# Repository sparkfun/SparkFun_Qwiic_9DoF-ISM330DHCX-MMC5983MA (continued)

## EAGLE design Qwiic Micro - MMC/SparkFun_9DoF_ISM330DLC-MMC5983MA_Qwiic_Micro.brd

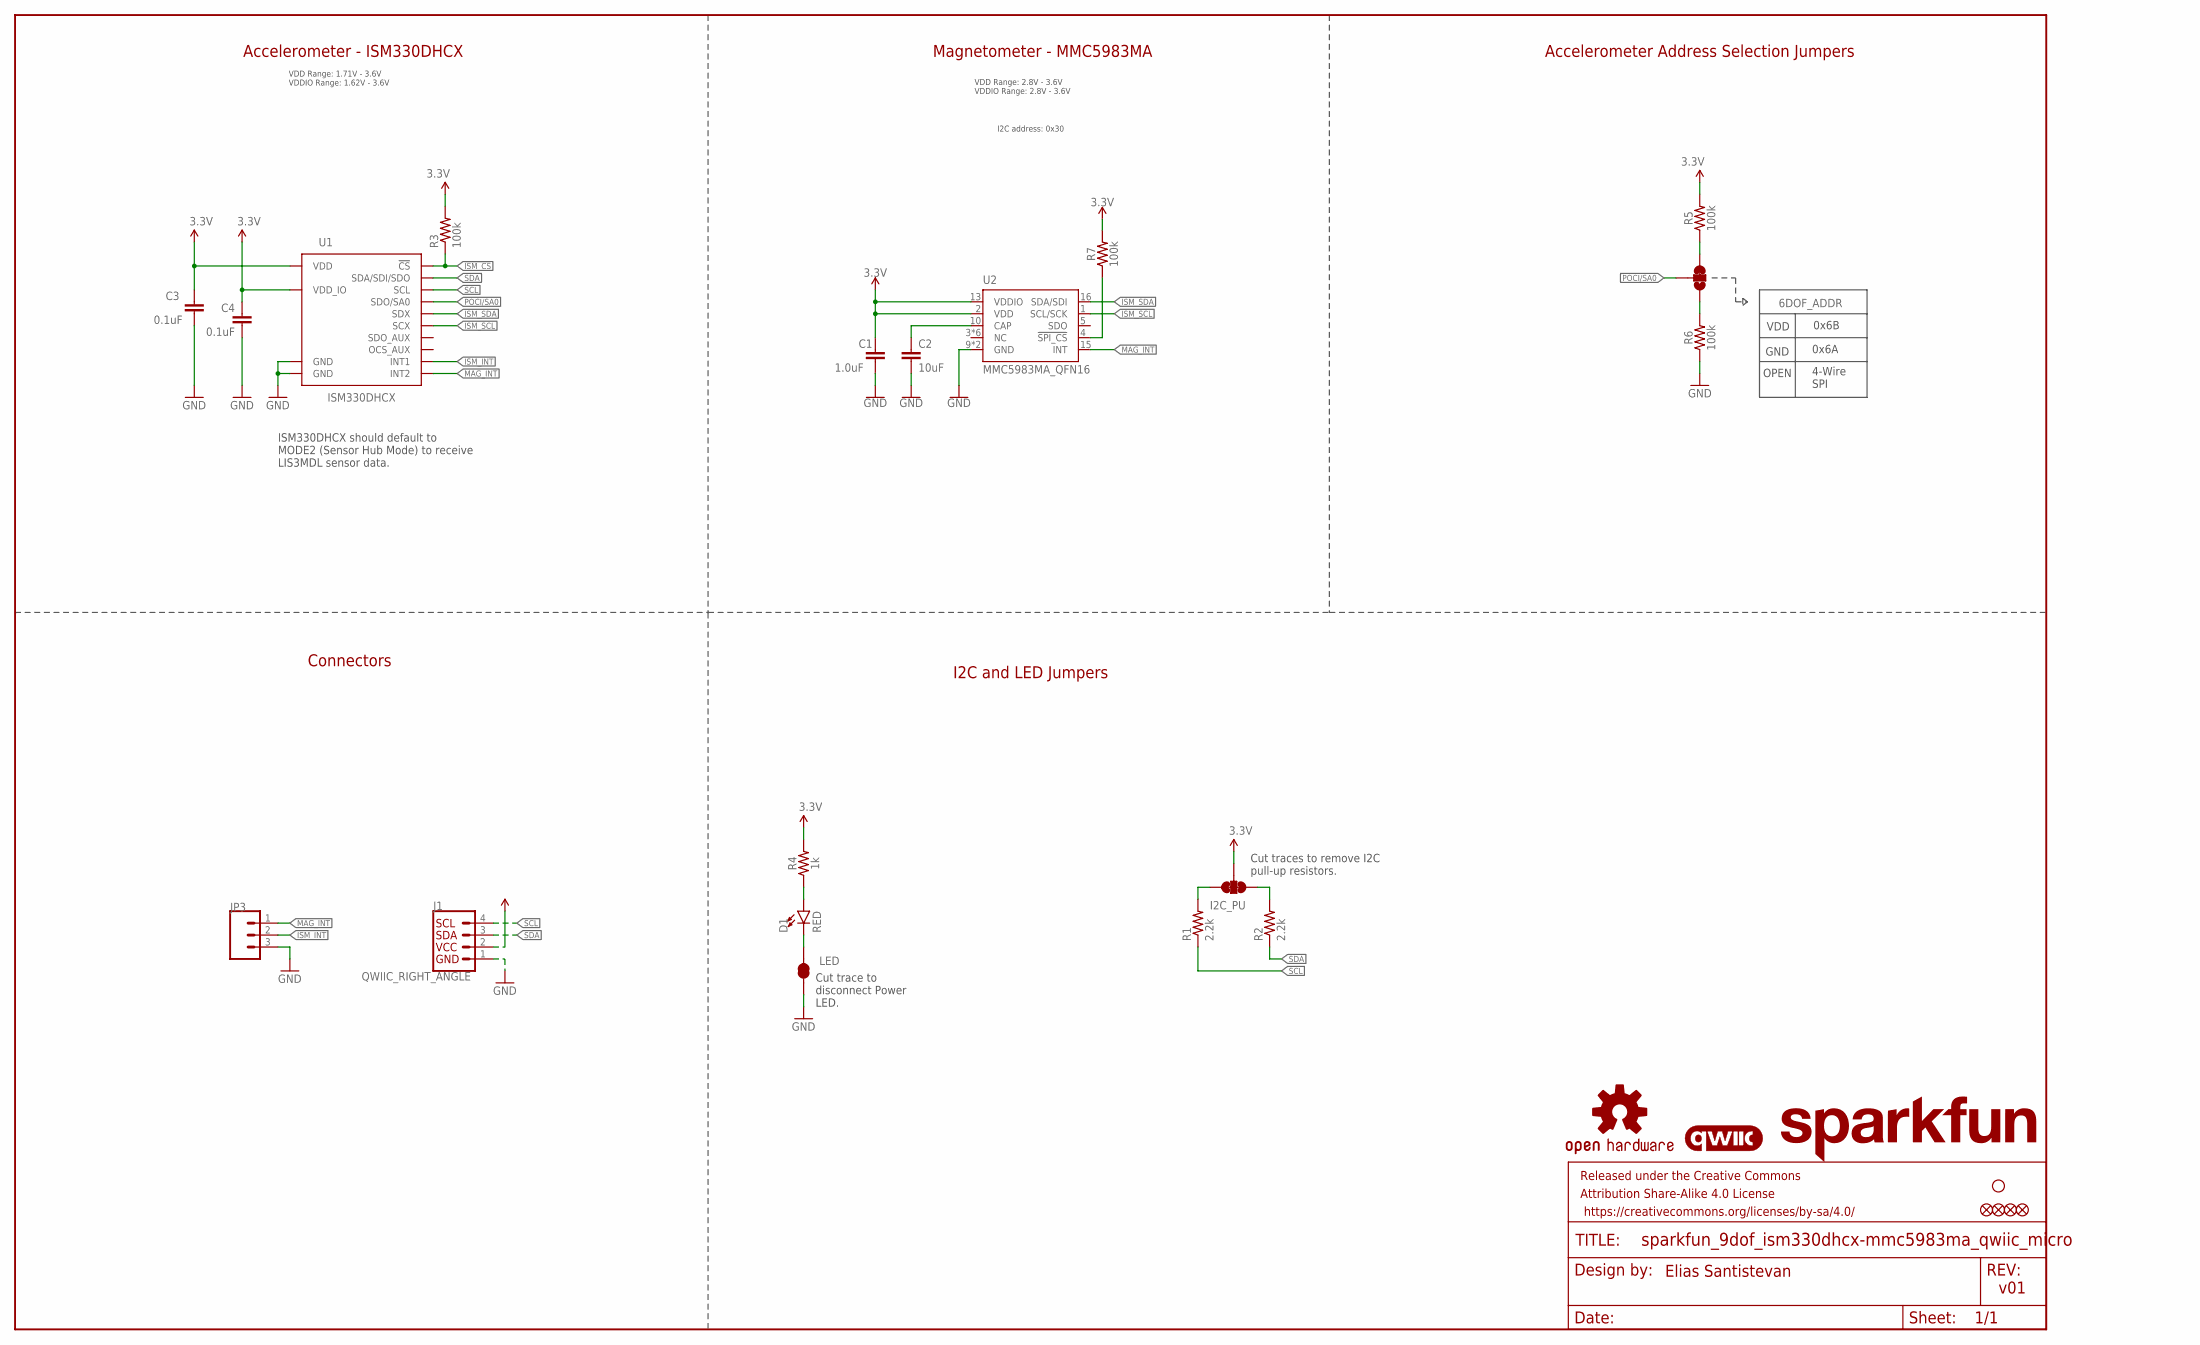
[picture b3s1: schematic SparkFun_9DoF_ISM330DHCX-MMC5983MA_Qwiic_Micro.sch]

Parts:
6DOF_ADDR: JUMPER-SMT_3_1-NC_TRACE_SILK; SMT-JUMPER_3_1-NC_TRACE_SILK
C1: 1.0uF; 0402-TIGHT
C2: 10uF; 0402-TIGHT
C3, C4: 0.1uF; 0402-TIGHT
D1: RED; 0402-TIGHT
FD1, FD2: FIDUCIALUFIDUCIAL; FIDUCIAL-MICRO
FID1, FID2: FIDUCIALUFIDUCIAL; FIDUCIAL-MICRO
FRAME2: FRAME-LEDGER; CREATIVE_COMMONS
I2C_PU: S_MODE; SMT-JUMPER_3_2-NC_TRACE_SILK
J1: QWIIC_RIGHT_ANGLE; JST04_1MM_RA
JP3: IO; 1X03_NO_SILK
LED: JUMPER-SMT_2_NC_TRACE_SILK; SMT-JUMPER_2_NC_TRACE_SILK
LOGO1: QWIIC_LOGO_4MM; QWIIC_4MM
LOGO2: OSHW-LOGOMINI; OSHW-LOGO-MINI
LOGO3: SFE_LOGO_NAMEBLANK; BLANK
R1, R2: 2.2k; 0402-TIGHT
R3, R5, R6, R7: 100k; 0402-TIGHT
R4: 1k; 0402-TIGHT
STANDOFF2: STAND-OFFTIGHT; STAND-OFF-TIGHT
U1: ISM330DHCX; LGA-14L
U2: MMC5983MA_QFN16; LGA-16-3X3MM-4X4PINS

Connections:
3.3V: C1.1, C3.1, C4.1, I2C_PU.2, J1.2, R3.2, R4.2, R5.2, R7.2, U1.P5 (VDD_IO), U1.P8 (VDD), U2.2 (VDD), U2.13 (VDDIO)
!ISM_CS!: R3.1, U1.P12 (!CS!)
!MAG_CS!: R7.1, U2.4 (!SPI_CS!)
CAP: C2.1, U2.10 (CAP)
GND: C1.2, C2.2, C3.2, C4.2, J1.1, JP3.3, LED.1, R6.1, U1.P6 (GND), U1.P7 (GND), U2.9 (GND), U2.11 (GND)
ISM_INT: JP3.2, U1.P4 (INT1)
ISM_SCL: U1.P3 (SCX), U2.1 (SCL/SCK)
ISM_SDA: U1.P2 (SDX), U2.16 (SDA/SDI)
MAG_INT: JP3.1, U1.P9 (INT2), U2.15 (INT)
unnamed: 6DOF_ADDR.3, R5.1
unnamed: D1.A, R4.1
unnamed: D1.C, LED.2
unnamed: I2C_PU.1, R1.2
unnamed: I2C_PU.3, R2.2
unnamed: 6DOF_ADDR.1, R6.2
POCI/SA0: 6DOF_ADDR.2, U1.P1 (SDO/SA0)
SCL: J1.4, R1.1, U1.P13 (SCL)
SDA: J1.3, R2.1, U1.P14 (SDA/SDI/SDO)

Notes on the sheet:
Accelerometer - ISM330DHCX
Cut traces to remove I2C pull-up resistors.
ISM330DHCX should default to MODE2 (Sensor Hub Mode) to receive LIS3MDL sensor data.
VDD Range: 1.71V - 3.6V VDDIO Range: 1.62V - 3.6V
v01
Cut trace to disconnect Power LED.
Connectors
VDD
GND
OPEN
0x6B
0x6A
4-Wire SPI
Elias Santistevan
VDD Range: 2.8V - 3.6V VDDIO Range: 2.8V - 3.6V
Magnetometer - MMC5983MA
Accelerometer Address Selection Jumpers
I2C and LED Jumpers
I2C address: 0x30

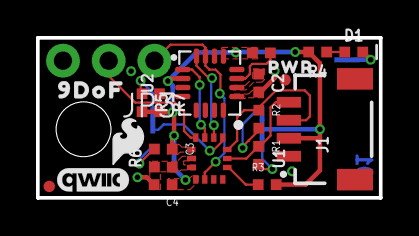
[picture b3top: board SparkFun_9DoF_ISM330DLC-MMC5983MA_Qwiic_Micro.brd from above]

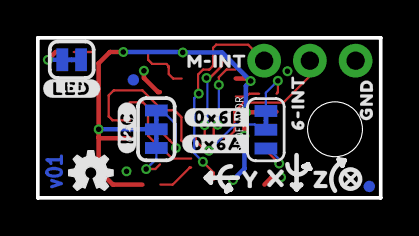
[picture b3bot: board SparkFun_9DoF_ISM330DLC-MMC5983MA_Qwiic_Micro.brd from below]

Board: 2 copper layers, 19.1 x 8.9 mm, 41 parts (16 on the bottom side), 18 nets.

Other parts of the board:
U$1: GND4
U$2: M#INT8
U$3: 6#INT8
U$4: #0X6A#13
U$5: #0X6B#13
U$6: 9DOF5985
U$16: #LED#11
U$25: #I2C#11
U$28: PWR8
U$29: SFE_LOGO_FLAME_.1
U$37: X2114
U$38: Y2115
U$39: Z2116

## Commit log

2022-04-25 Restricts ground pour around Magnetometer, renames 6DoF I2C nets
2022-04-26 Fixes many silk errors
    * Adds polarity marker to MMC - previous one is eaten by PTH silk
    * Adds flags to interrupt silk
    * Moves resistor to make room for SDA and SCL silk
    * Renames "MAG SDA/SCL" net to "AUX SDA/SCL"
    * Rotates version number in copper
2022-04-26 Changes main 6DoF to new part
2022-04-26 Renames board files to reflect 6DoF part change
2022-04-26 Updates silk on board to reflect part change
2022-04-26 Fixes clearance issue
2022-04-26 Updates text in schematic referencing old part
2022-04-26 Adds gerbers
2022-06-08 Updates routing
2022-06-08 More updates to the routing
2022-06-08 Finishes routing
2022-06-08 Vias applied
2022-06-08 Adds text to schematic, adds jumpers to SDX and SCX
2022-06-08 Adds silk
2022-06-08 Adds a via
2022-06-08 Removes old designs
2022-06-08 Removes old library
2022-06-08 Rolls to version v02
2022-06-09 Rotates R7 to make room for silk, nudges R2 to make room for silk
    * Fixes some DRC errors
2022-06-09 Nudges some vias around to avoid collisions with silk
2022-06-09 Rolls to v10, adds silk to accelerometer address selection jumper
    * Adds note to schematic about magnetometer address not being affected by accelerometer address selection
    * Increases size of VCC and address text
2022-06-10 Adds production files
2022-06-10 Renames "Qwiic" folder to "Hardware"
2022-06-10 Adds version to production zip file
2022-06-13 Qwiic 9dof TB board update to match design changes
    Design changed to not use sensor hub mode. Changed testbed to reflect those changes
2022-06-13 Revert "Qwiic 9dof TB board update to match design changes"
    This reverts commit 867b655bef504f495645ea868ae599dd038fac2f.
